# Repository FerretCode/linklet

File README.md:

# linklet

A modular, LoRa enabled sensor bus

## Overview

- Linklet is an custom PCB design with an STM32 and RFM69HCW LoRa modules for sensing and IoT operations
- The base board exposes 1x UART and 1x I2C interface for basic sensors
- The board is powered over micro-USB
- Linklet also exposes a 1x8 pin socket connector for carrying daughter boards
    - The connector has 1x UART and 1x I2C interface for daughter boards
    - It makes it easy for swapping out different sensor arrays on the fly

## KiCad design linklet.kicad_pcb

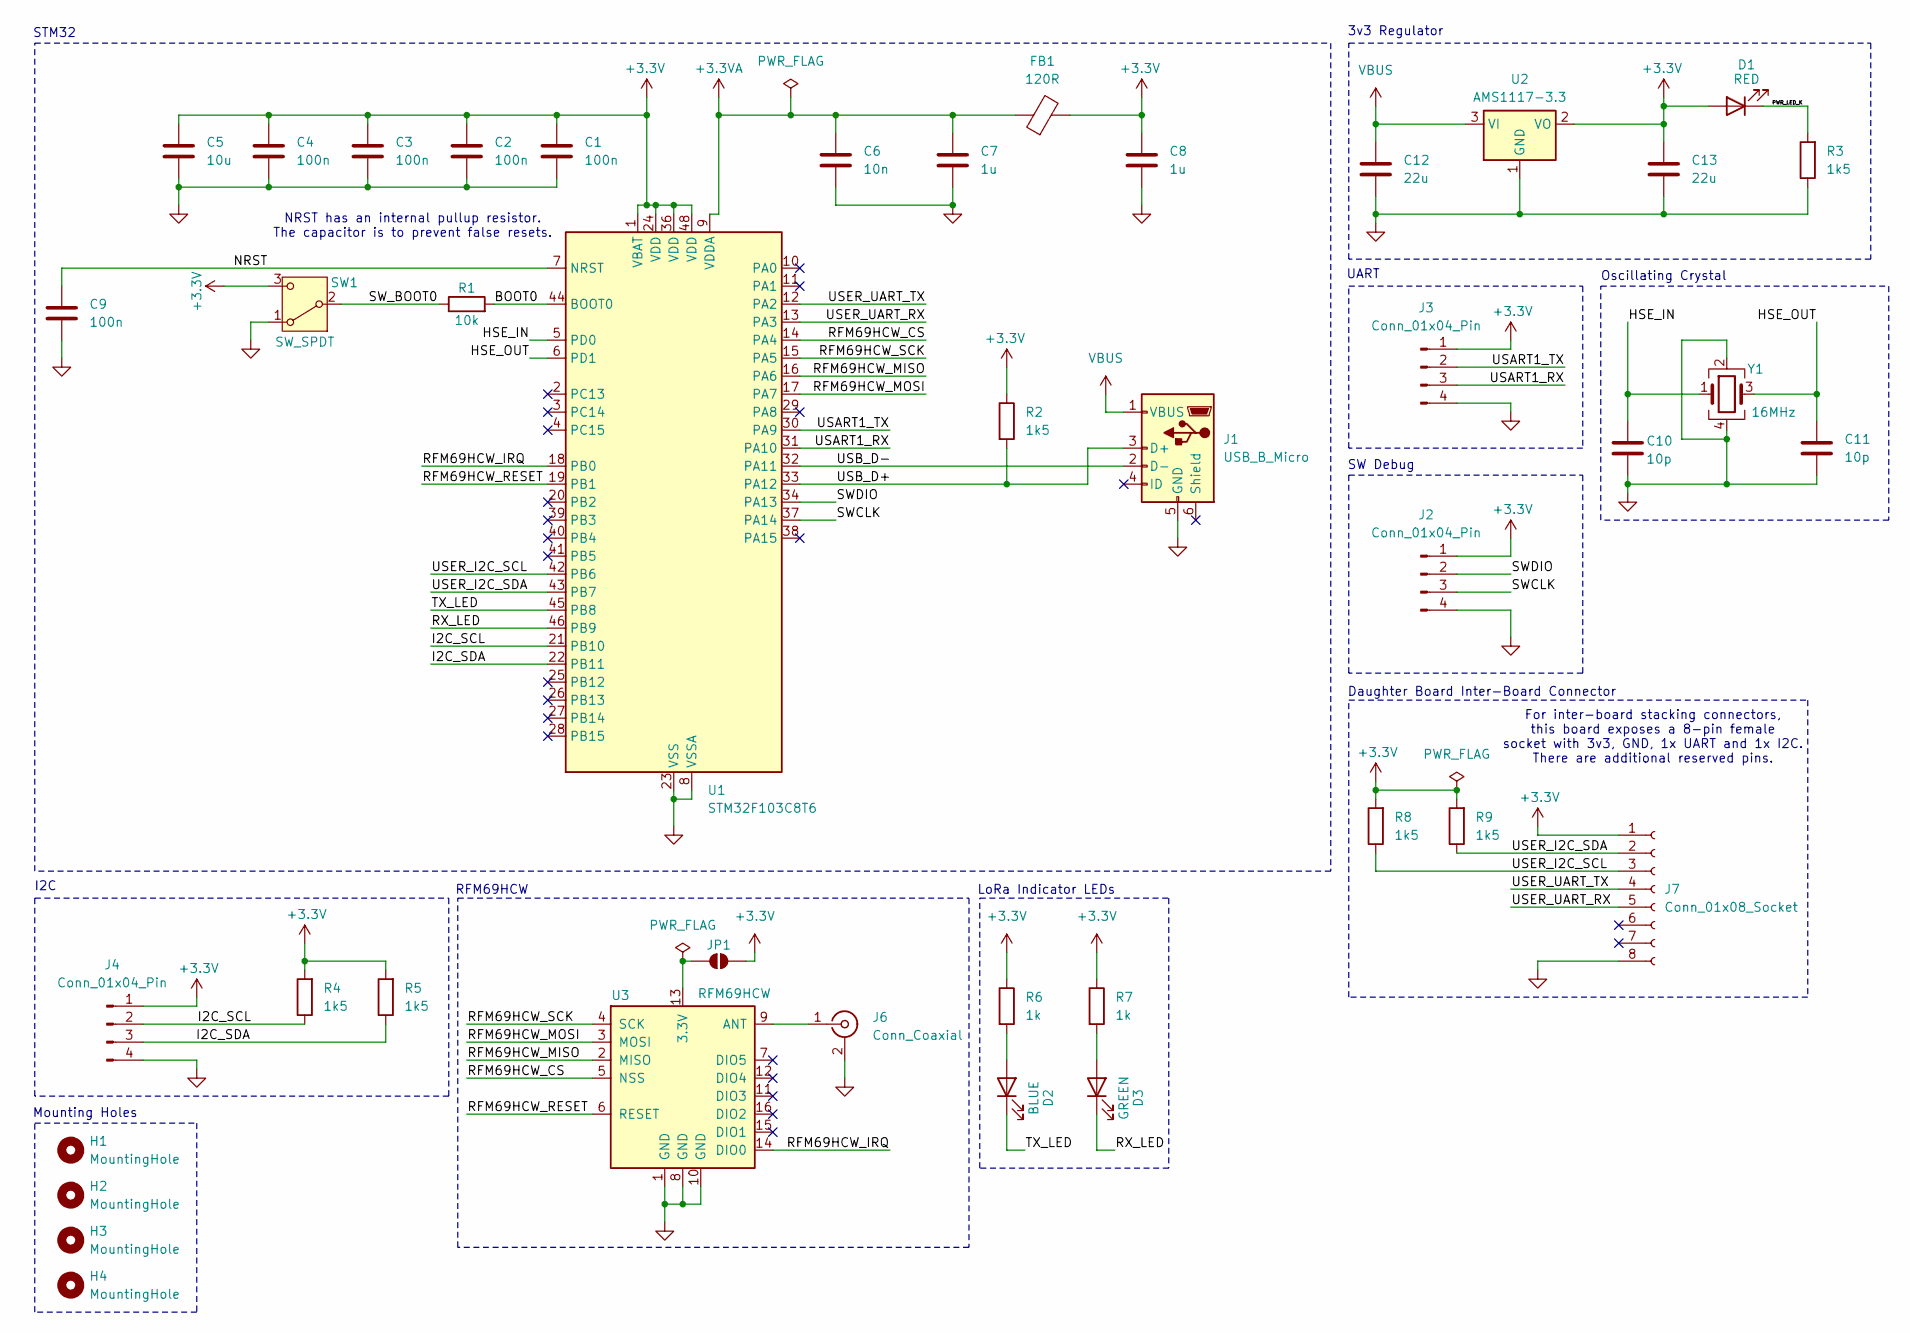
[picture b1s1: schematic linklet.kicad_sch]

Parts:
C1, C2, C3, C4, C9: 100n; C_0402_1005Metric
C5: 10u; C_0603_1608Metric
C6: 10n; C_0402_1005Metric
C7, C8: 1u; C_0402_1005Metric
C10, C11: 10p; C_0402_1005Metric
C12, C13: 22u; C_0805_2012Metric
D1: RED; LED_0603_1608Metric
D2: BLUE; LED_0603_1608Metric
D3: GREEN; LED_0603_1608Metric
FB1: 120R; L_0603_1608Metric
H1, H2, H3, H4: MountingHole; MountingHole_2.2mm_M2
J1: USB_B_Micro; USB_Micro-B_Wuerth_629105150521
J2, J3, J4: Conn_01x04_Pin; PinHeader_1x04_P2.54mm_Vertical
J6: Conn_Coaxial; SMA_Molex_73251-1153_EdgeMount_Horizontal
J7: Conn_01x08_Socket; PinHeader_1x08_P2.54mm_Vertical
JP1: SolderJumper_2_Open; SolderJumper-2_P1.3mm_Open_Pad1.0x1.5mm
R1: 10k; R_0402_1005Metric
R2, R3, R4, R5, R8, R9: 1k5; R_0402_1005Metric
R6, R7: 1k; R_0402_1005Metric
SW1: SW_SPDT; SW_SPDT_PCM12
U1: STM32F103C8T6; LQFP-48_7x7mm_P0.5mm
U2: AMS1117-3.3; SOT-223-3_TabPin2
U3: RFM69HCW; HOPERF_RFM9XW_SMD
Y1: 16MHz; Crystal_SMD_3225-4Pin_3.2x2.5mm

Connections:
+3.3V: C1.1, C2.1, C3.1, C4.1, C5.1, C8.1, C13.1, D1.2 (A), FB1.2, J2.1, J3.1, J4.1, J7.1, JP1.1 (A), R2.1, R4.2, R5.2, R6.1, R7.1, R8.2, R9.2, SW1.3 (C), U1.1 (VBAT), U1.24 (VDD), U1.36 (VDD), U1.48 (VDD), U2.2 (VO)
+3.3VA: C6.1, C7.1, FB1.1, U1.9 (VDDA)
/BOOT0: R1.2, U1.44 (BOOT0)
/HSE_IN: C10.1, U1.5 (PD0), Y1.1
/HSE_OUT: C11.1, U1.6 (PD1), Y1.3
/I2C_SCL: J4.2, R4.1, U1.21 (PB10)
/I2C_SDA: J4.3, R5.1, U1.22 (PB11)
/NRST: C9.1, U1.7 (NRST)
/PWR_LED_K: D1.1 (K), R3.2
/RFM69HCW_CS: U1.14 (PA4), U3.5 (NSS)
/RFM69HCW_IRQ: U1.18 (PB0), U3.14 (DIO0)
/RFM69HCW_MISO: U1.16 (PA6), U3.2 (MISO)
/RFM69HCW_MOSI: U1.17 (PA7), U3.3 (MOSI)
/RFM69HCW_RESET: U1.19 (PB1), U3.6 (RESET)
/RFM69HCW_SCK: U1.15 (PA5), U3.4 (SCK)
/RX_LED: D3.1 (K), U1.46 (PB9)
/SWCLK: J2.3, U1.37 (PA14)
/SWDIO: J2.2, U1.34 (PA13)
/SW_BOOT0: R1.1, SW1.2 (B)
/TX_LED: D2.1 (K), U1.45 (PB8)
/USART1_RX: J3.3, U1.31 (PA10)
/USART1_TX: J3.2, U1.30 (PA9)
/USB_D+: J1.3 (D+), R2.2, U1.33 (PA12)
/USB_D-: J1.2 (D-), U1.32 (PA11)
/USER_I2C_SCL: J7.3, R8.1, U1.42 (PB6)
/USER_I2C_SDA: J7.2, R9.1, U1.43 (PB7)
/USER_UART_RX: J7.5, U1.13 (PA3)
/USER_UART_TX: J7.4, U1.12 (PA2)
GND: C1.2, C2.2, C3.2, C4.2, C5.2, C6.2, C7.2, C8.2, C9.2, C10.2, C11.2, C12.2, C13.2, J1.5 (GND), J2.4, J3.4, J4.4, J6.2 (Ext), J7.8, R3.1, SW1.1 (A), U1.8 (VSSA), U1.23 (VSS), U1.35 (VSS), U1.47 (VSS), U2.1 (GND), U3.1 (GND), U3.8 (GND), U3.10 (GND), Y1.2, Y1.4
unnamed: D2.2 (A), R6.2
unnamed: D3.2 (A), R7.2
unnamed: J6.1 (In), U3.9 (ANT)
unnamed: JP1.2 (B), U3.13 (3.3V)
VBUS: C12.1, J1.1 (VBUS), U2.3 (VI)

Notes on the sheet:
Daughter Board Inter-Board Connector
SW Debug
Mounting Holes
NRST has an internal pullup resistor. The capacitor is to prevent false resets.
UART
STM32
For inter-board stacking connectors, this board exposes a 8-pin female socket with 3v3, GND, 1x UART and 1x I2C. There are additional reserved pins.
3v3 Regulator
Oscillating Crystal
I2C
RFM69HCW
LoRa Indicator LEDs

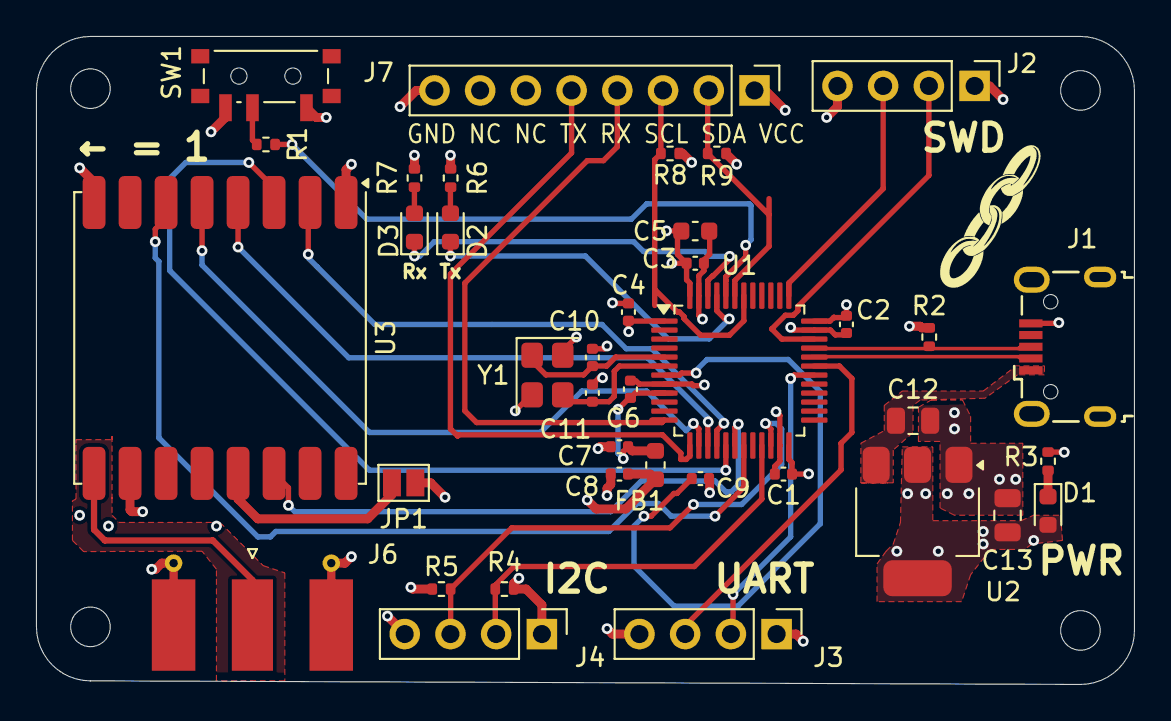
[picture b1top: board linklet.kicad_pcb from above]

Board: 4 copper layers, 61.0 x 36.0 mm, 42 parts (0 on the bottom side), 34 nets.

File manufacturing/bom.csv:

Comment;Designator;Footprint;Supplier and ref
Conn_Coaxial;J6;SMA_Molex_73251-1153_EdgeMount_Horizontal;C43302011
100n;C1,C4,C3,C9,C2;C_0402_1005Metric;C309458
Conn_01x08_Socket;J7;PinHeader_1x08_P2.54mm_Vertical;C9900212703
1k5;R8,R3,R9,R4,R2,R5;R_0402_1005Metric;C25867
10u;C5;C_0603_1608Metric;C96446
1k;R7,R6;R_0402_1005Metric;C49652832
USB_B_Micro;J1;USB_Micro-B_Wuerth_629105150521;C2894326
1u;C7,C8;C_0402_1005Metric;C52923
Conn_01x04_Pin;J2,J4,J3;PinHeader_1x04_P2.54mm_Vertical;C5116483
STM32F103C8T6;U1;LQFP-48_7x7mm_P0.5mm;C8734
SW_SPDT;SW1;SW_SPDT_PCM12;C221841
10n;C6;C_0402_1005Metric;C3855387
AMS1117-3.3;U2;SOT-223-3_TabPin2;C6186
16MHz;Y1;Crystal_SMD_3225-4Pin_3.2x2.5mm;C112972
10p;C11,C10;C_0402_1005Metric;C106199
22u;C13,C12;C_0805_2012Metric;C452754
10k;R1;R_0402_1005Metric;C1002
220R;FB1;L_0603_1608Metric;C66810
RED;D1,D2,D3;LED_0603_1608Metric;C965798

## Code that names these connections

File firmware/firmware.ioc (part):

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Mcu.Name=STM32F103C(8-B)Tx
Mcu.Package=LQFP48
Mcu.UserName=STM32F103C8Tx
PA10.Mode=Asynchronous
PA10.Signal=USART1_RX
PA11.Mode=Device
PA11.Signal=USB_DM
PA12.Mode=Device
PA12.Signal=USB_DP
PA2.Mode=Asynchronous
PA2.Signal=USART2_TX
PA3.Mode=Asynchronous
PA3.Signal=USART2_RX
PA9.Mode=Asynchronous
PA9.Signal=USART1_TX
PB10.Mode=I2C
PB10.Signal=I2C2_SCL
PB11.Mode=I2C
PB11.Signal=I2C2_SDA
PB6.Mode=I2C
PB6.Signal=I2C1_SCL
PB7.Mode=I2C
PB7.Signal=I2C1_SDA
PD0-OSC_IN.Mode=HSE-External-Oscillator
PD0-OSC_IN.Signal=RCC_OSC_IN
PD1-OSC_OUT.Mode=HSE-External-Oscillator
PD1-OSC_OUT.Signal=RCC_OSC_OUT
RCC.SYSCLKFreq_VALUE=48000000
RCC.SYSCLKSource=RCC_SYSCLKSOURCE_PLLCLK
board=custom

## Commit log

2025-09-22 add project
2025-09-22 update silkscreen
2025-09-22 switch to using grounded coplanar waveguide for RF feed line
2025-09-29 add manufacturing files
2025-11-13 add pdf
2025-12-24 bootstrap firmware
2025-12-24 add img
